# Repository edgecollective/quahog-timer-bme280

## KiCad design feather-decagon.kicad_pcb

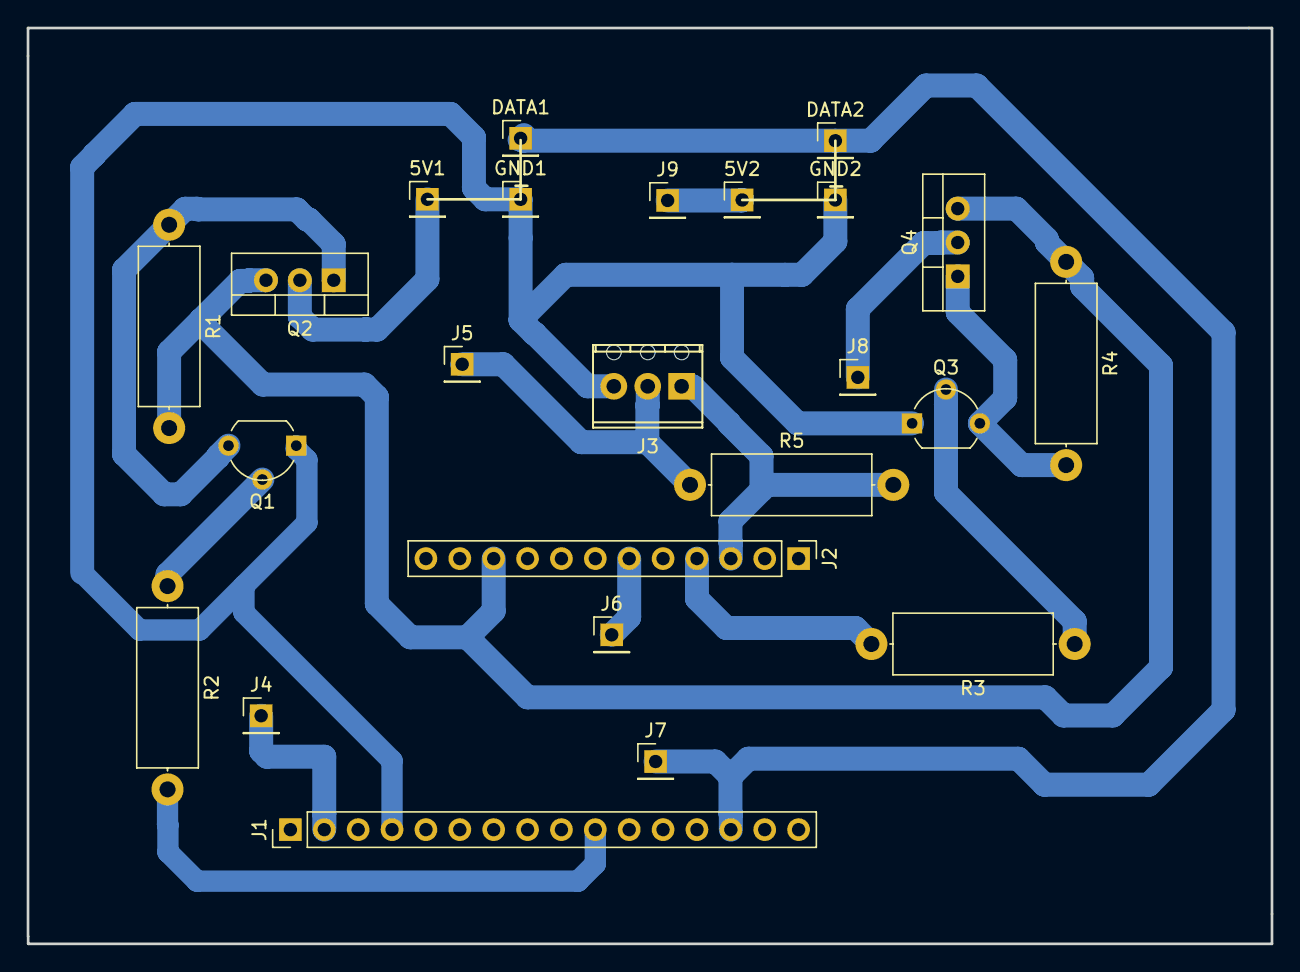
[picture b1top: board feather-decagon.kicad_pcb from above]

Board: 2 copper layers, 93.3 x 68.7 mm, 24 parts (0 on the bottom side), 13 nets.

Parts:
5V1, 5V2: Conn_01x01; Pin_Header_Straight_1x01_Pitch2.54mm
DATA1, DATA2: Conn_01x01; Pin_Header_Straight_1x01_Pitch2.54mm
GND1, GND2: Conn_01x01; Pin_Header_Straight_1x01_Pitch2.54mm
J1: Conn_01x16_Female; Pin_Header_Straight_1x16_Pitch2.54mm
J2: Conn_01x12_Female; Pin_Header_Straight_1x12_Pitch2.54mm
J3: Screw_Terminal_01x03; TerminalBlock_Phoenix_MPT-2.54mm_3pol
J4, J5, J6, J7, J8, J9: Conn_01x01; Pin_Header_Straight_1x01_Pitch2.54mm
Q1, Q3: Q_NPN_EBC; TO-92_Molded_Wide
Q2, Q4: Q_PMOS_GDS; TO-220-3_Vertical
R1, R4: 100K; R_Axial_DIN0414_L11.9mm_D4.5mm_P15.24mm_Horizontal
R2, R3: 10K; R_Axial_DIN0414_L11.9mm_D4.5mm_P15.24mm_Horizontal
R5: 4.7K; R_Axial_DIN0414_L11.9mm_D4.5mm_P15.24mm_Horizontal

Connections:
unnamed: 5V1.1, Q2.2
unnamed: 5V2.1, J8.1, J9.1, Q4.2
unnamed: DATA1.1, DATA2.1, J1.14, J2.6, J6.1, J7.1
unnamed: GND1.1, GND2.1, J1.4, J3.3, Q1.1, Q3.1
unnamed: J1.2, J3.2, J4.1, J5.1, R5.1
unnamed: J1.10, R2.2
unnamed: J2.3, J3.1, R5.2
unnamed: J2.4, R3.2
unnamed: J2.10, Q2.3, Q4.3, R1.2, R4.1
unnamed: Q1.2, R2.1
unnamed: Q1.3, Q2.1, R1.1
unnamed: Q3.2, R3.1
unnamed: Q3.3, Q4.1, R4.2
